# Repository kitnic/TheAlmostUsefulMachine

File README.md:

# TheAlmostUsefulMachine

More at  http://tinkerlog.com/2016/06/03/the-almost-useful-machine/

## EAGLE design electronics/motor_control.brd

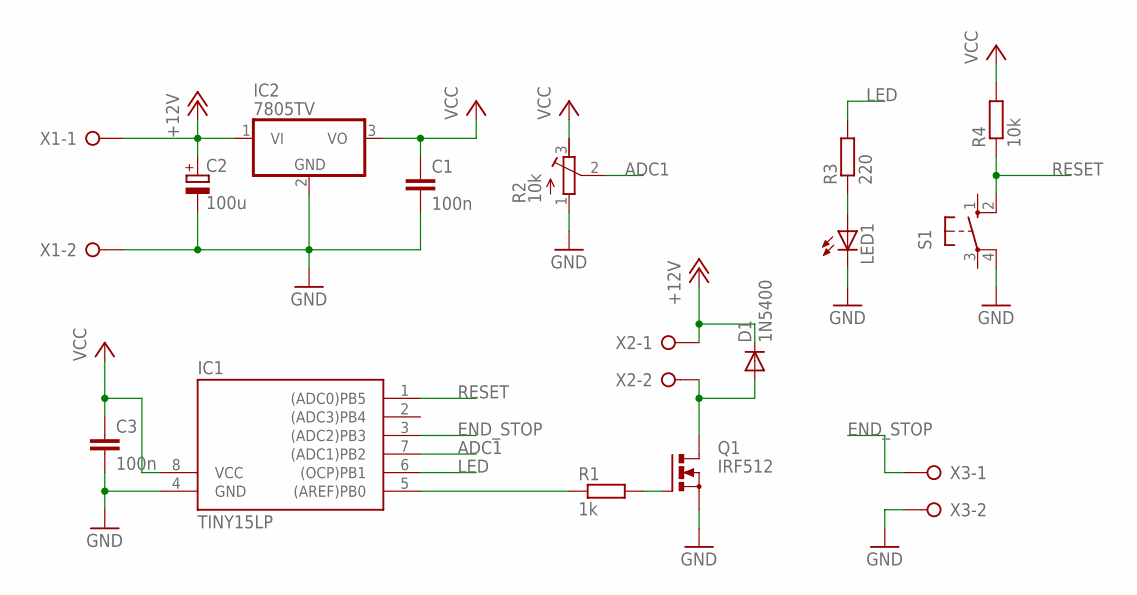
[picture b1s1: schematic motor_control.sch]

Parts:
C1, C3: 100n; C025-025X050
C2: 100u; E2,5-6E
D1: 1N5400; DO201-15
IC1: TINY15LP; DIL08
IC2: 7805TV; TO220V
LED1: LED5MM
Q1: IRF512; TO220BV
R1: 1k; 0309/10
R2: 10k; RTRIM3296W
R3: 220; 0309/10
R4: 10k; 0309/10
S1: 40-XX; B3F-40XX
X1, X2, X3: W237-02P; W237-132

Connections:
+12V: C2.+, D1.C, IC2.1 (VI), X1.1, X2.1
ADC1: IC1.7 ((ADC1)PB2), R2.2 (S)
END_STOP: IC1.3 ((ADC2)PB3), X3.1
GND: C1.2, C2.-, C3.2, IC1.4 (GND), IC2.2 (GND), LED1.K (C), Q1.S, R2.1 (A), S1.4 (P1), X1.2, X3.2
LED: IC1.6 ((OCP)PB1), R3.2
unnamed: LED1.A, R3.1
unnamed: Q1.G, R1.2
unnamed: IC1.5 ((AREF)PB0), R1.1
unnamed: D1.A, Q1.D, X2.2
RESET: IC1.1 ((ADC0)PB5), R4.1, S1.2 (S1)
VCC: C1.1, C3.1, IC1.8 (VCC), IC2.3 (VO), R2.3 (E), R4.2

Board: 2 copper layers, 16 parts (0 on the bottom side), 11 nets, no tracks yet.

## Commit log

2016-06-03 initial
